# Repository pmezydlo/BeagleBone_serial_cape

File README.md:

<h1>Beagle Bone serial cape</h1>

<h2>License</h2>

<h2>Images</h2>

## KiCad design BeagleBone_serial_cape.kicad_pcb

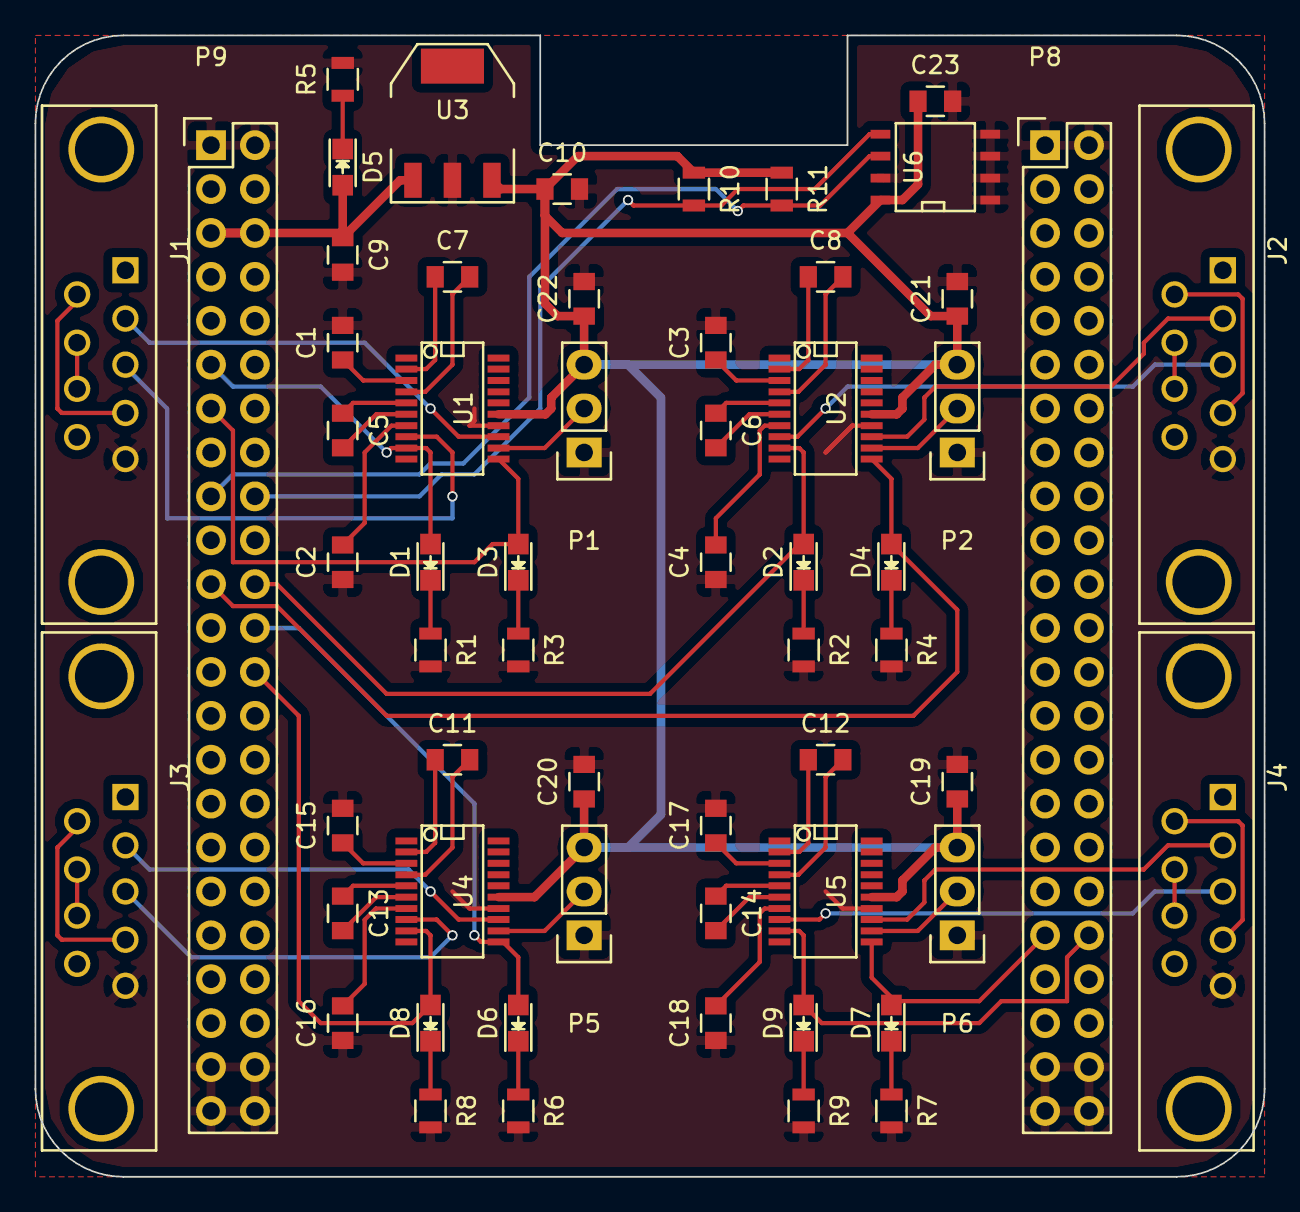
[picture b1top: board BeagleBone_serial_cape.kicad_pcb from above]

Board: 2 copper layers, 71.1 x 66.0 mm, 59 parts (0 on the bottom side), 66 nets.

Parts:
C1, C2, C3, C4, C5, C6, C7, C8, C11, C12, C13, C14, C15, C16, C17, C18: 100n; C_0805
C9: 10u; C_0805
C10: 3.3u; C_0805
C19, C20, C21, C22, C23: 0.1u; C_0805
D1, D2, D3, D4, D6, D7, D8, D9: LED; LED_0805
D5: PWR; LED_0805
J1, J2, J3, J4: DB9; DB9MD
P1, P2, P5, P6: CONN_01X03; Pin_Header_Straight_1x03
P8, P9: CONN_02X23; Pin_Header_Straight_2x23
R1, R2, R3, R4, R5, R6, R7, R8, R9: 1k; R_0805
R10, R11: 10k; R_0805
U1, U2, U4, U5: MAX3227; SSOP-20
U3: LT1129MPST-3.3; SOT-223
U6: 24C512; SOIC-8-N

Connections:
+3V3: C10.1, C19.1, C20.1, C21.1, C22.1, C23.1, P1.3, P2.3, P5.3, P6.3, R10.1, R11.1, U1.15, U2.15, U3.3, U4.15, U5.15, U6.8
GND: C1.2, C2.1, C3.2, C4.1, C9.2, C10.2, C15.2, C16.1, C17.2, C18.1, C19.2, C20.2, C21.2, C22.2, C23.2, J1.5, J2.5, J3.5, J4.5, P1.1, P2.1, P5.1, P6.1, P8.1, P8.2, P8.43, P8.44, P8.45, P8.46, P9.1, P9.2, P9.43, P9.44, P9.45, P9.46, R1.2, R2.2, R3.2, R4.2, R5.2, R6.2, R7.2, R8.2, R9.2, U1.14, U2.14, U3.2, U4.14, U5.14, U6.1, U6.2, U6.3, U6.4, U6.7
unnamed: C1.1, U1.3
unnamed: C2.2, U1.7
unnamed: C3.1, U2.3
unnamed: C4.2, U2.7
unnamed: C5.1, U1.5
unnamed: C5.2, U1.6
unnamed: C6.1, U2.5
unnamed: C6.2, U2.6
unnamed: C7.1, U1.2
unnamed: C7.2, U1.4
unnamed: C8.1, U2.2
unnamed: C8.2, U2.4
unnamed: C11.1, U4.2
unnamed: C11.2, U4.4
unnamed: C12.1, U5.2
unnamed: C12.2, U5.4
unnamed: C13.1, U4.5
unnamed: C13.2, U4.6
unnamed: C14.1, U5.5
unnamed: C14.2, U5.6
unnamed: C15.1, U4.3
unnamed: C16.2, U4.7
unnamed: C17.1, U5.3
unnamed: C18.2, U5.7
unnamed: D1.1, R1.1
unnamed: D1.2, P9.11, U1.9
unnamed: D2.1, R2.1
unnamed: D2.2, P9.22, U2.9
unnamed: D3.1, R3.1
unnamed: D3.2, P9.13, U1.11
unnamed: D4.1, R4.1
unnamed: D4.2, P9.21, U2.11
unnamed: D5.1, R5.1
unnamed: D6.1, R6.1
unnamed: D6.2, P9.24, U4.11
unnamed: D7.1, R7.1
unnamed: D7.2, P8.37, U5.11
unnamed: D8.1, R8.1
unnamed: D8.2, P9.26, U4.9
unnamed: D9.1, R9.1
unnamed: D9.2, P8.38, U5.9
unnamed: J1.2, U1.13
unnamed: J1.3, U1.8
unnamed: J1.4, J1.6
unnamed: J1.7, J1.8
unnamed: J2.2, U2.13
unnamed: J2.3, U2.8
unnamed: J2.4, J2.6
unnamed: J2.7, J2.8
unnamed: J3.2, U4.13
unnamed: J3.3, U4.8
unnamed: J3.4, J3.6
unnamed: J3.7, J3.8
unnamed: J4.2, U5.13
unnamed: J4.3, U5.8
unnamed: J4.4, J4.6
unnamed: J4.7, J4.8
unnamed: P1.2, U1.12
unnamed: P2.2, U2.12
unnamed: P5.2, U4.12
unnamed: P6.2, U5.12
unnamed: P9.17, R11.2, U6.6
unnamed: P9.18, R10.2, U6.5
VCC: C9.1, D5.2, P9.5, P9.6, U3.1

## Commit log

2017-02-21 initial commit 1.electrical schematic 2.arragement of elements
2017-02-21 routing pcb add more photos Signed-off-by: Patryk Mezydlo <mezydlo.p@gmail.com>
2017-02-22 add EEPROM for auto-detect add thicker traces fixed GND and 3.3v routing add bypass capacitors
2017-02-22 add bypass capacitor for EEPROM memory
